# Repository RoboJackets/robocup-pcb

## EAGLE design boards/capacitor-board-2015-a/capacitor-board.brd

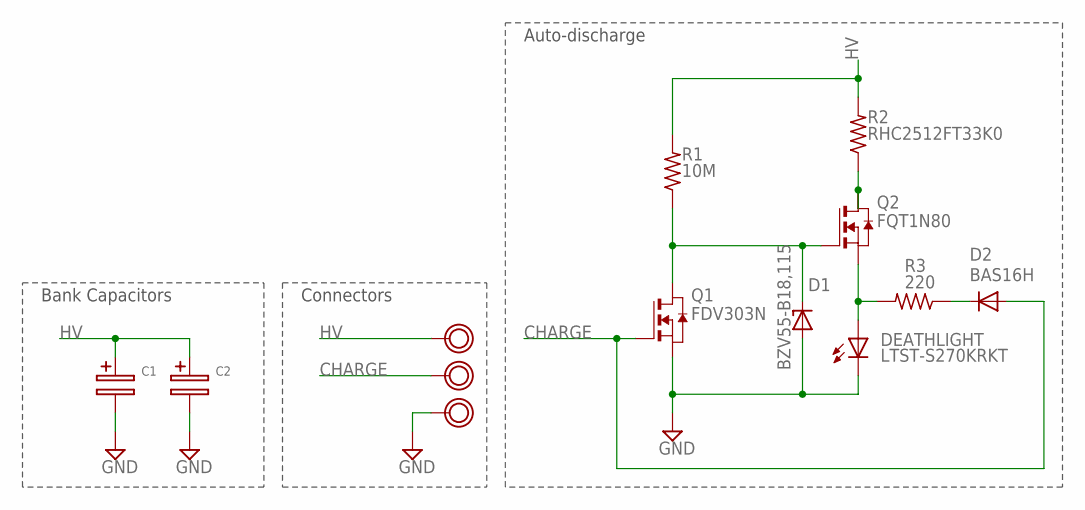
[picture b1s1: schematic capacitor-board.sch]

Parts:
C1, C2: RC_CAPHORIZ; 25MM-DIA_HORIZ
D1: BZV55-B18,115; SOD80C
D2: BAS16H; SOD323-W
DEATHLIGHT: LTST-S270KRKT; CHIPLED_0603
Q1: FDV303N; SOT-23
Q2: FQT1N80; SOT223
R1: 10M; R0603
R2: RHC2512FT33K0; R2512
R3: 220; R0603
U$1, U$2, U$3: VIA_TP; VIA_2MM

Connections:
CHARGE: D2.A, Q1.3 (G), U$2.P$1
GND: C1.-, C2.-, D1.A, DEATHLIGHT.C, Q1.2 (S), U$3.P$1
HV: C1.+, C2.+, R1.2, R2.2, U$1.P$1
unnamed: D1.C, Q1.1 (D), Q2.1 (G), R1.1
unnamed: Q2.2 (D), Q2.4 (D2), R2.1
unnamed: DEATHLIGHT.A, Q2.3 (S), R3.2
unnamed: D2.C, R3.1

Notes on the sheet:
Bank Capacitors
Connectors
Auto-discharge

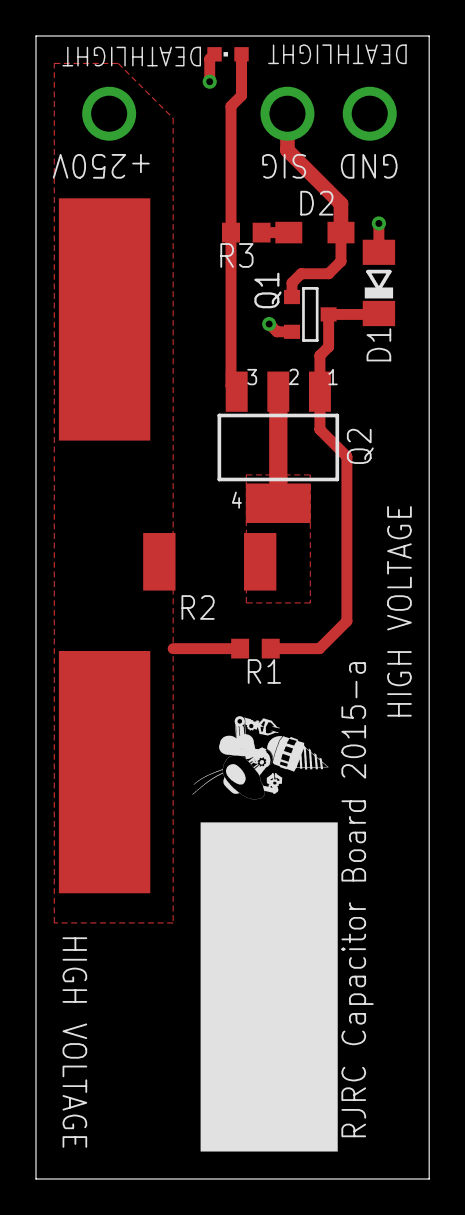
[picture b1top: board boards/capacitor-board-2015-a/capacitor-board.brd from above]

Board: 2 copper layers, 21.8 x 63.5 mm, 14 parts (0 on the bottom side), 7 nets.

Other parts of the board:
U$4: ROBOBUZZ_0.4X

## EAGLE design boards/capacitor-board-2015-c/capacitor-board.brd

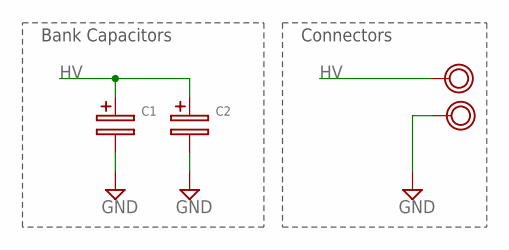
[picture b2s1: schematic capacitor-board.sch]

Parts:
C1, C2: RC_CAPHORIZ; 25MM-DIA_HORIZ
U$1, U$3: VIA_TP; VIA_2MM

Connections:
GND: C1.-, C2.-, U$3.P$1
HV: C1.+, C2.+, U$1.P$1

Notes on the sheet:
Bank Capacitors
Connectors

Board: 2 copper layers, 6 parts (1 on the bottom side), 2 nets, no tracks yet.

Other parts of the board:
U$2, U$4: ROBOBUZZ_0.4X

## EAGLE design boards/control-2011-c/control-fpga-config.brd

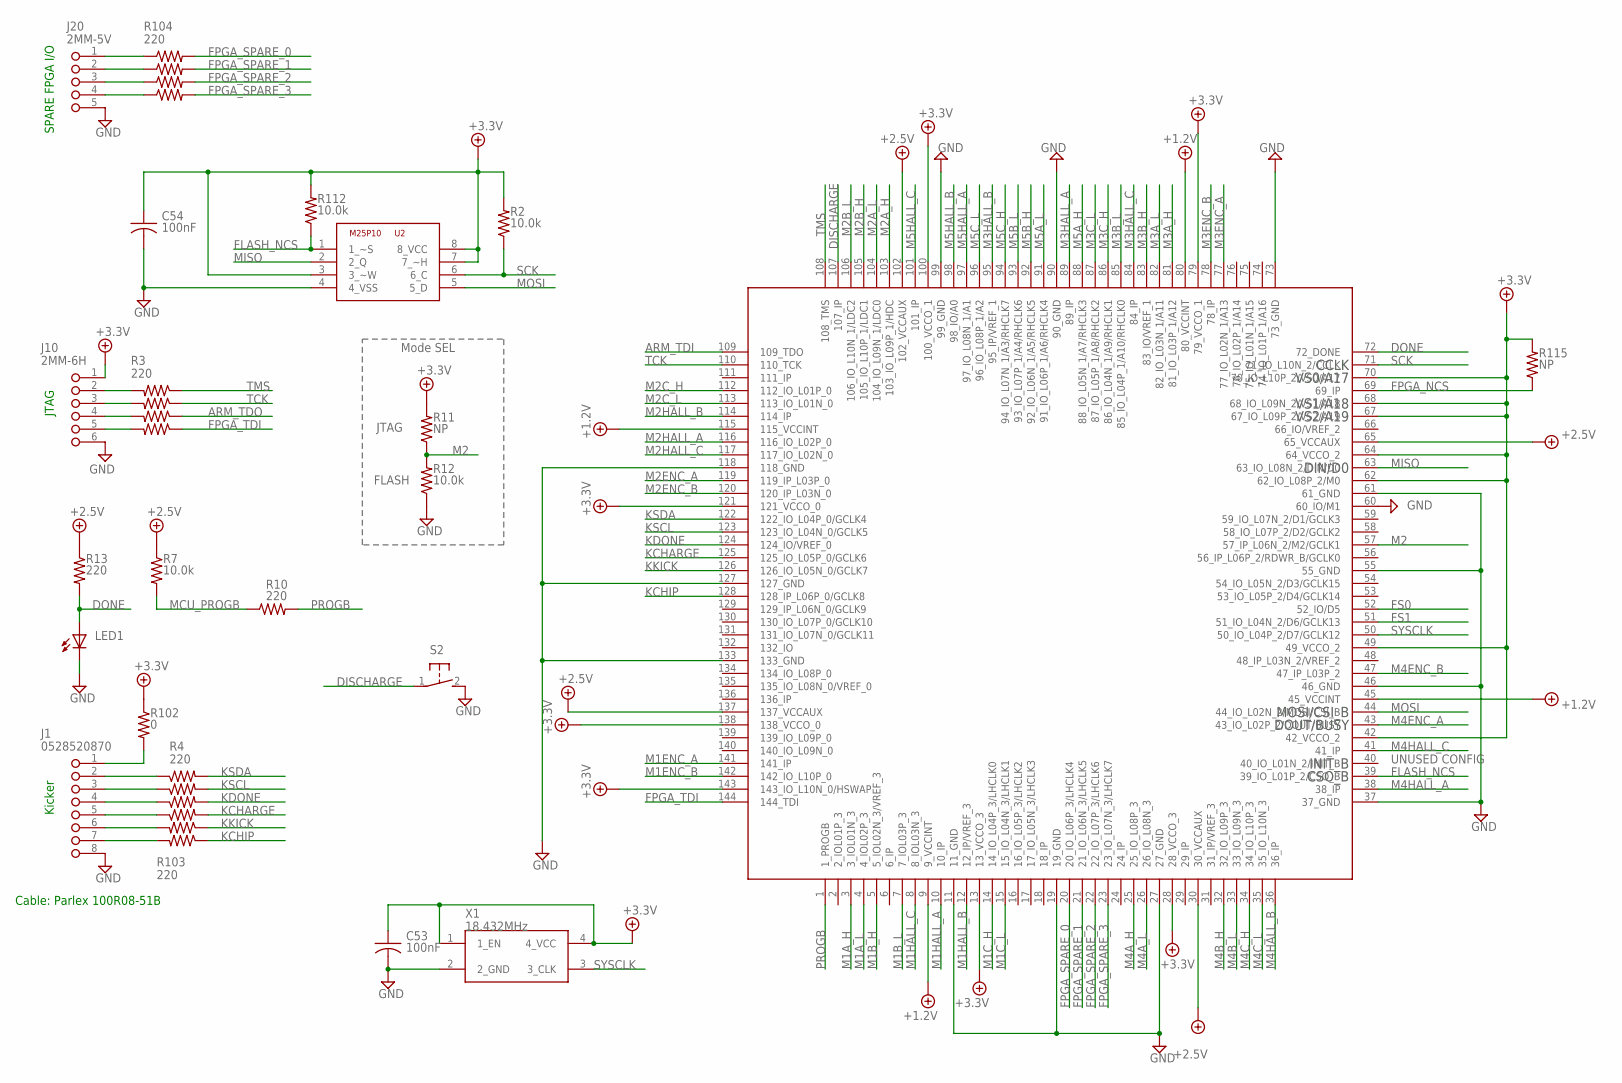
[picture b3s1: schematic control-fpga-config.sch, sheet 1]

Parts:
C53, C54: 100nF; C0603
J1: 0528520870
J10: 2MM-6H; 2MM-6-H
J20: 2MM-5V; 2MM-5-V
LED1: LEDCHIP-LED0603; CHIP-LED0603
R2, R7, R12, R112: 10.0k; R0603
R3, R4, R104: 220; RA_4_1206
R10, R13: 220; R0603
R11, R115: NP; R0603
R102: 0; R0603
R103: 220; RA_2_0606
S2: 31-XX; B3F-31XX
U1: XC3S100E; TQFP144
U2: M25P10; SO08
X1: 18.432MHz; XTAL_LCC

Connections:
+1.2V: U1.9 (9_VCCINT), U1.45 (45_VCCINT), U1.80 (80_VCCINT), U1.115 (115_VCCINT); also elsewhere on the board
+2.5V: R7.1, R13.1, U1.30 (30_VCCAUX), U1.65 (65_VCCAUX), U1.102 (102_VCCAUX), U1.137 (137_VCCAUX); also elsewhere on the board
+3.3V: C53.1, C54.1, J10.1, R2.2, R11.2, R102.1, R112.2, R115.2, U1.13 (13_VCCO_3), U1.28 (28_VCCO_3), U1.42 (42_VCCO_2), U1.49 (49_VCCO_2), U1.62 (62_IO_L08P_2/M0), U1.64 (64_VCCO_2), U1.67 (67_IO_L09P_2/VS2/A19), U1.68 (68_IO_L09N_2/VS1/A18), U1.70 (70_IO_L10P_2/VS0/A17), U1.79 (79_VCCO_1), U1.100 (100_VCCO_1), U1.121 (121_VCCO_0), U1.138 (138_VCCO_0), U1.143 (143_IO_L10N_0/HSWAP), U2.3 (3_~W), U2.7 (7_~H), U2.8 (8_VCC), X1.1 (1_EN), X1.4 (4_VCC); also elsewhere on the board
ARM_TDI: U1.109 (109_TDO); also elsewhere on the board
ARM_TDO: R3.5; also elsewhere on the board
DISCHARGE: S2.1, U1.107 (107_IP)
DONE: LED1.A, R13.2, U1.72 (72_DONE)
FLASH_NCS: R112.1, U1.39 (39_IO_L01P_2/CSO_B), U2.1 (1_~S); also elsewhere on the board
FPGA_NCS: R115.1, U1.69 (69_IP); also elsewhere on the board
FPGA_SPARE_0: R104.2, U1.20 (20_IO_L06P_3/LHCLK4)
FPGA_SPARE_1: R104.4, U1.21 (21_IO_L06N_3/LHCLK5)
FPGA_SPARE_2: R104.6, U1.22 (22_IO_L07P_3/LHCLK6)
FPGA_SPARE_3: R104.8, U1.23 (23_IO_L07N_3/LHCLK7)
FPGA_TDI: R3.7, U1.144 (144_TDI)
FS0: U1.52 (52_IO/D5); also elsewhere on the board
FS1: U1.51 (51_IO_L04N_2/D6/GCLK13); also elsewhere on the board
GND: C53.2, C54.2, J1.8, J10.6, J20.5, LED1.C, R12.1, S2.2 (S), U1.11 (11_GND), U1.19 (19_GND), U1.27 (27_GND), U1.37 (37_GND), U1.46 (46_GND), U1.55 (55_GND), U1.60 (60_IO/M1), U1.61 (61_GND), U1.73 (73_GND), U1.90 (90_GND), U1.99 (99_GND), U1.118 (118_GND), U1.127 (127_GND), U1.133 (133_GND), U2.4 (4_VSS), X1.2 (2_GND); also elsewhere on the board
KCHARGE: R4.2, U1.125 (125_IO_L05P_0/GCLK6)
KCHIP: R103.3, U1.128 (128_IP_L06P_0/GCLK8)
KDONE: R4.4, U1.124 (124_IO/VREF_0)
KKICK: R103.1, U1.126 (126_IO_L05N_0/GCLK7)
KSCL: R4.6, U1.123 (123_IO_L04N_0/GCLK5)
KSDA: R4.8, U1.122 (122_IO_L04P_0/GCLK4)
M1A_H: U1.3 (3_IOL01N_3); also elsewhere on the board
M1A_L: U1.4 (4_IOL02P_3); also elsewhere on the board
M1B_H: U1.5 (5_IOL02N_3/VREF_3); also elsewhere on the board
M1B_L: U1.7 (7_IOL03P_3); also elsewhere on the board
M1C_H: U1.14 (14_IO_L04P_3/LHCLK0); also elsewhere on the board
M1C_L: U1.15 (15_IO_L04N_3/LHCLK1); also elsewhere on the board
M1ENC_A: U1.141 (141_IP); also elsewhere on the board
M1ENC_B: U1.142 (142_IO_L10P_0); also elsewhere on the board
M1HALL_A: U1.10 (10_IP); also elsewhere on the board
M1HALL_B: U1.12 (12_IP/VREF_3); also elsewhere on the board
M1HALL_C: U1.8 (8_IOL03N_3); also elsewhere on the board
M2: R11.1, R12.2, U1.57 (57_IP_L06N_2/M2/GCLK1)
M2A_H: U1.103 (103_IO_L09P_1/HDC); also elsewhere on the board
M2A_L: U1.104 (104_IO_L09N_1/LDC0); also elsewhere on the board
M2B_H: U1.105 (105_IO_L10P_1/LDC1); also elsewhere on the board
M2B_L: U1.106 (106_IO_L10N_1/LDC2); also elsewhere on the board
M2C_H: U1.112 (112_IO_L01P_0); also elsewhere on the board
M2C_L: U1.113 (113_IO_L01N_0); also elsewhere on the board
M2ENC_A: U1.119 (119_IP_L03P_0); also elsewhere on the board
M2ENC_B: U1.120 (120_IP_L03N_0); also elsewhere on the board
M2HALL_A: U1.116 (116_IO_L02P_0); also elsewhere on the board
M2HALL_B: U1.114 (114_IP); also elsewhere on the board
M2HALL_C: U1.117 (117_IO_L02N_0); also elsewhere on the board
M3A_H: U1.81 (81_IO_L03P_1/A12); also elsewhere on the board
M3A_L: U1.82 (82_IO_L03N_1/A11); also elsewhere on the board
M3B_H: U1.83 (83_IO/VREF_1); also elsewhere on the board
M3B_L: U1.85 (85_IO_L04P_1/A10/RHCLK0); also elsewhere on the board
M3C_H: U1.86 (86_IO_L04N_1/A9/RHCLK1); also elsewhere on the board
M3C_L: U1.87 (87_IO_L05P_1/A8/RHCLK2); also elsewhere on the board
M3ENC_A: U1.77 (77_IO_L02N_1/A13); also elsewhere on the board
M3ENC_B: U1.78 (78_IP); also elsewhere on the board
M3HALL_A: U1.89 (89_IP); also elsewhere on the board
M3HALL_B: U1.95 (95_IP/VREF_1); also elsewhere on the board
M3HALL_C: U1.84 (84_IP); also elsewhere on the board
M4A_H: U1.25 (25_IO_L08P_3); also elsewhere on the board
M4A_L: U1.26 (26_IO_L08N_3); also elsewhere on the board
M4B_H: U1.32 (32_IO_L09P_3); also elsewhere on the board
M4B_L: U1.33 (33_IO_L09N_3); also elsewhere on the board
M4C_H: U1.34 (34_IO_L10P_3); also elsewhere on the board
M4C_L: U1.35 (35_IO_L10N_3); also elsewhere on the board
M4ENC_A: U1.43 (43_IO_L02P_2/DOUT/BUSY); also elsewhere on the board
M4ENC_B: U1.47 (47_IP_L03P_2); also elsewhere on the board
M4HALL_A: U1.38 (38_IP); also elsewhere on the board
M4HALL_B: U1.36 (36_IP); also elsewhere on the board
M4HALL_C: U1.41 (41_IP); also elsewhere on the board
M5A_H: U1.88 (88_IO_L05N_1/A7/RHCLK3); also elsewhere on the board
M5A_L: U1.91 (91_IO_L06P_1/A6/RHCLK4); also elsewhere on the board
M5B_H: U1.92 (92_IO_L06N_1/A5/RHCLK5); also elsewhere on the board
M5B_L: U1.93 (93_IO_L07P_1/A4/RHCLK6); also elsewhere on the board
M5C_H: U1.94 (94_IO_L07N_1/A3/RHCLK7); also elsewhere on the board
M5C_L: U1.96 (96_IO_L08P_1/A2); also elsewhere on the board
M5HALL_A: U1.97 (97_IO_L08N_1/A1); also elsewhere on the board
M5HALL_B: U1.98 (98_IO/A0); also elsewhere on the board
M5HALL_C: U1.101 (101_IP); also elsewhere on the board
MCU_PROGB: R7.2, R10.1; also elsewhere on the board
MISO: U1.63 (63_IO_L08N_2/DIN/D0), U2.2 (2_Q); also elsewhere on the board
MOSI: U1.44 (44_IO_L02N_2/MOSI/CSI_B), U2.5 (5_D); also elsewhere on the board
unnamed: J10.3, R3.4
unnamed: J10.5, R3.8
unnamed: J1.2, R4.7
unnamed: J1.3, R4.5
unnamed: J1.4, R4.3
unnamed: J1.5, R4.1
unnamed: J10.4, R3.6
unnamed: J10.2, R3.2
unnamed: J1.6, R103.2
unnamed: J1.7, R103.4
unnamed: J1.1, R102.2
unnamed: J20.3, R104.5
unnamed: J20.2, R104.3
unnamed: J20.1, R104.1
unnamed: J20.4, R104.7
PROGB: R10.2, U1.1 (1_PROGB)
SCK: R2.1, U1.71 (71_IO_L10N_2/CCLK), U2.6 (6_C); also elsewhere on the board
SYSCLK: U1.50 (50_IO_L04P_2/D7/GCLK12), X1.3 (3_CLK); also elsewhere on the board
TCK: R3.3, U1.110 (110_TCK); also elsewhere on the board
TMS: R3.1, U1.108 (108_TMS); also elsewhere on the board

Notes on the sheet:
JTAG
FLASH
Mode SEL
Kicker
UNUSED CONFIG
SPARE FPGA I/O
Cable: Parlex 100R08-51B
INIT_B
CCLK
CSO_B
MOSI/CSI_B
DOUT/BUSY
DIN/D0
VS1/A18
VS2/A19
VS0/A17

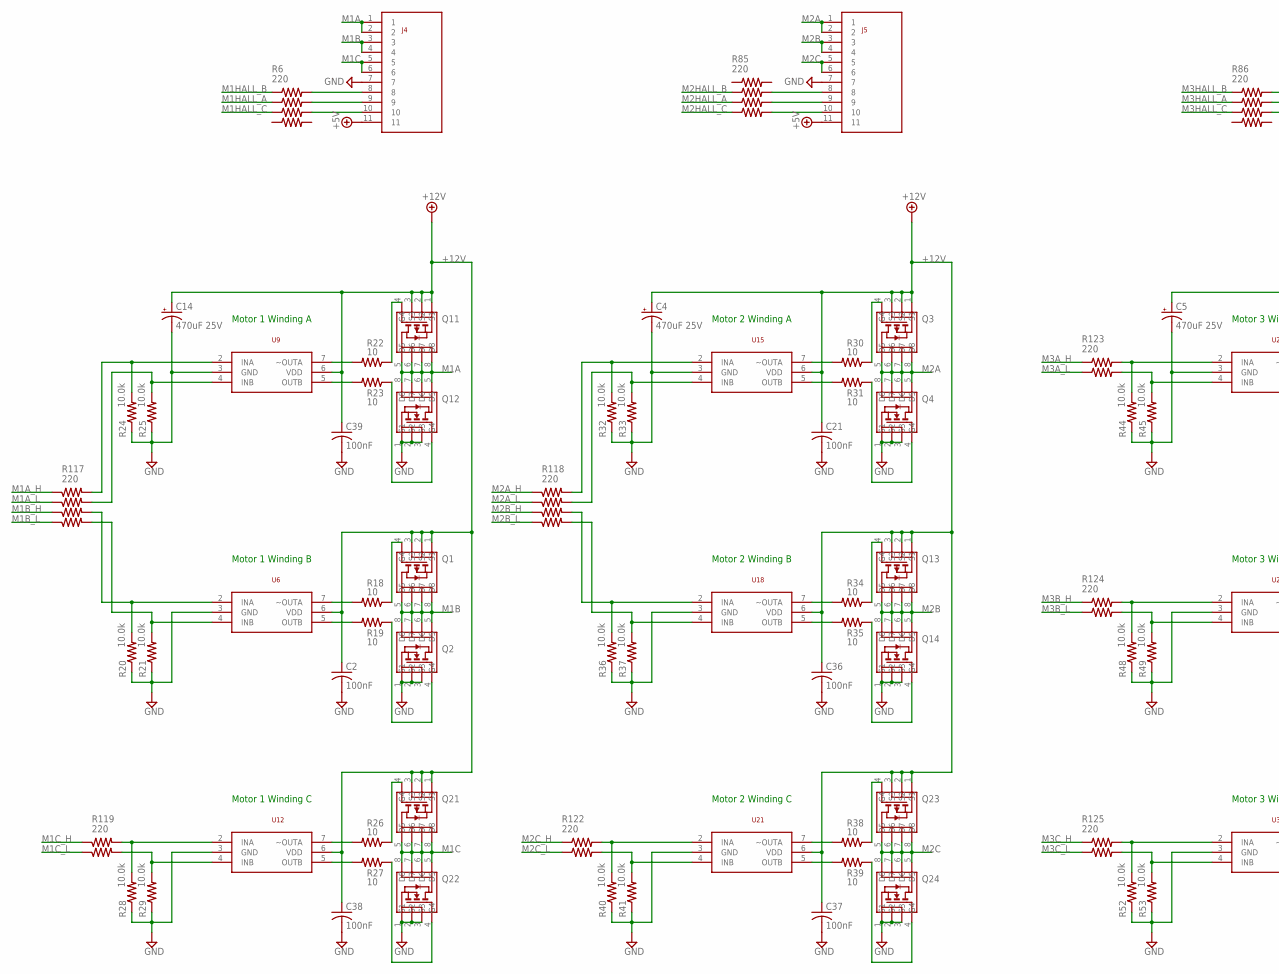
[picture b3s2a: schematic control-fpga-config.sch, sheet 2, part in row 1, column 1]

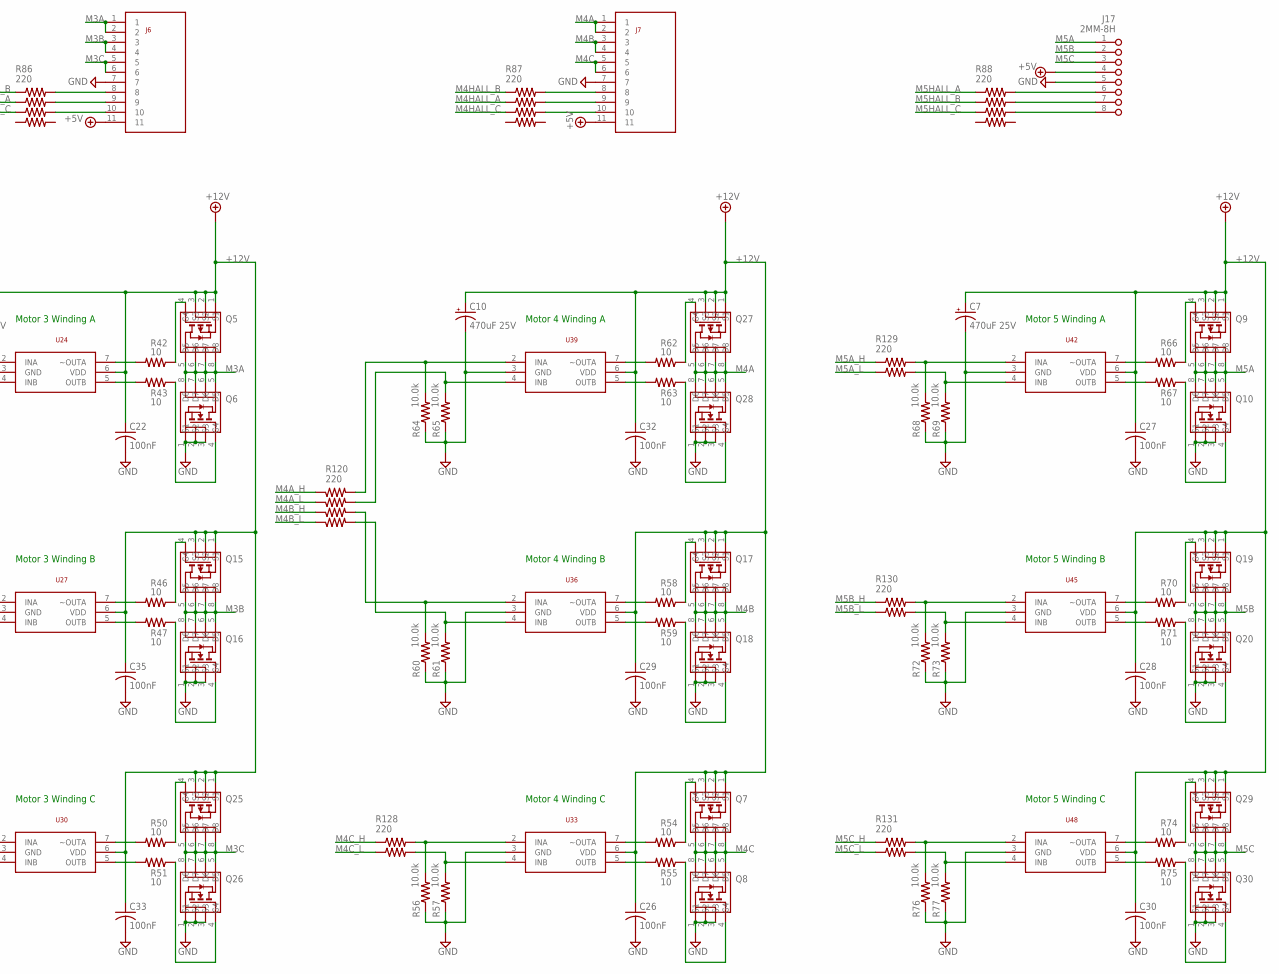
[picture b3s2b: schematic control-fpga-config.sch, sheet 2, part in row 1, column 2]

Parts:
C2, C21, C22, C26, C27, C28, C29, C30, C32, C33, C35, C36, C37, C38, C39: 100nF; C0603
C4, C5, C7, C10, C14: 470uF 25V; PANASONIC_G
J4, J5, J6, J7: Molex 0522711179; FH_11_HOR
J17: 2MM-8H; 2MM-8-H
Q1, Q3, Q5, Q7, Q9, Q11, Q13, Q15, Q17, Q19, Q21, Q23, Q25, Q27, Q29: IRF9310TRPBF; SO8
Q2, Q4, Q6, Q8, Q10, Q12, Q14, Q16, Q18, Q20, Q22, Q24, Q26, Q28, Q30: IRF8734TRPBF; SO8
R6, R85, R86, R87, R88, R117, R118, R120: 220; RA_4_1206
R18, R19, R22, R23, R26, R27, R30, R31, R34, R35, R38, R39, R42, R43, R46, R47, R50, R51, R54, R55, R58, R59, R62, R63, R66, R67, R70, R71, R74, R75: 10; R0603
R20, R21, R24, R25, R28, R29, R32, R33, R36, R37, R40, R41, R44, R45, R48, R49, R52, R53, R56, R57, R60, R61, R64, R65, R68, R69, R72, R73, R76, R77: 10.0k; R0603
R119, R122, R123, R124, R125, R128, R129, R130, R131: 220; RA_2_0606
U6, U9, U12, U15, U18, U21, U24, U27, U30, U33, U36, U39, U42, U45, U48: TC4428; SO08

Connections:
+5V: J4.11, J5.11, J6.11, J7.11, J17.4; also elsewhere on the board
+12V: C2.1, C4.+, C5.+, C7.+, C10.+, C14.+, C21.1, C22.1, C26.1, C27.1, C28.1, C29.1, C30.1, C32.1, C33.1, C35.1, C36.1, C37.1, C38.1, C39.1, Q1.1 (S1), Q1.2 (S2), Q1.3 (S3), Q3.1 (S1), Q3.2 (S2), Q3.3 (S3), Q5.1 (S1), Q5.2 (S2), Q5.3 (S3), Q7.1 (S1), Q7.2 (S2), Q7.3 (S3), Q9.1 (S1), Q9.2 (S2), Q9.3 (S3), Q11.1 (S1), Q11.2 (S2), Q11.3 (S3), Q13.1 (S1), Q13.2 (S2), Q13.3 (S3), Q15.1 (S1), Q15.2 (S2), Q15.3 (S3), Q17.1 (S1), Q17.2 (S2), Q17.3 (S3), Q19.1 (S1), Q19.2 (S2), Q19.3 (S3), Q21.1 (S1), Q21.2 (S2), Q21.3 (S3), Q23.1 (S1), Q23.2 (S2), Q23.3 (S3), Q25.1 (S1), Q25.2 (S2), Q25.3 (S3), Q27.1 (S1), Q27.2 (S2), Q27.3 (S3), Q29.1 (S1), Q29.2 (S2), Q29.3 (S3), U6.6 (VDD), U9.6 (VDD), U12.6 (VDD), U15.6 (VDD), U18.6 (VDD), U21.6 (VDD), U24.6 (VDD), U27.6 (VDD), U30.6 (VDD), U33.6 (VDD), U36.6 (VDD), U39.6 (VDD), U42.6 (VDD), U45.6 (VDD), U48.6 (VDD); also elsewhere on the board
GND: C2.2, C4.-, C5.-, C7.-, C10.-, C14.-, C21.2, C22.2, C26.2, C27.2, C28.2, C29.2, C30.2, C32.2, C33.2, C35.2, C36.2, C37.2, C38.2, C39.2, J4.7, J5.7, J6.7, J7.7, J17.5, Q2.1 (S1), Q2.2 (S2), Q2.3 (S3), Q4.1 (S1), Q4.2 (S2), Q4.3 (S3), Q6.1 (S1), Q6.2 (S2), Q6.3 (S3), Q8.1 (S1), Q8.2 (S2), Q8.3 (S3), Q10.1 (S1), Q10.2 (S2), Q10.3 (S3), Q12.1 (S1), Q12.2 (S2), Q12.3 (S3), Q14.1 (S1), Q14.2 (S2), Q14.3 (S3), Q16.1 (S1), Q16.2 (S2), Q16.3 (S3), Q18.1 (S1), Q18.2 (S2), Q18.3 (S3), Q20.1 (S1), Q20.2 (S2), Q20.3 (S3), Q22.1 (S1), Q22.2 (S2), Q22.3 (S3), Q24.1 (S1), Q24.2 (S2), Q24.3 (S3), Q26.1 (S1), Q26.2 (S2), Q26.3 (S3), Q28.1 (S1), Q28.2 (S2), Q28.3 (S3), Q30.1 (S1), Q30.2 (S2), Q30.3 (S3), R20.1, R21.1, R24.1, R25.1, R28.1, R29.1, R32.1, R33.1, R36.1, R37.1, R40.1, R41.1, R44.1, R45.1, R48.1, R49.1, R52.1, R53.1, R56.1, R57.1, R60.1, R61.1, R64.1, R65.1, R68.1, R69.1, R72.1, R73.1, R76.1, R77.1, U6.3 (GND), U9.3 (GND), U12.3 (GND), U15.3 (GND), U18.3 (GND), U21.3 (GND), U24.3 (GND), U27.3 (GND), U30.3 (GND), U33.3 (GND), U36.3 (GND), U39.3 (GND), U42.3 (GND), U45.3 (GND), U48.3 (GND); also elsewhere on the board
M1A: J4.1, J4.2, Q11.5 (D5), Q11.6 (D6), Q11.7 (D7), Q11.8 (D8), Q12.5 (D5), Q12.6 (D6), Q12.7 (D7), Q12.8 (D8)
M1A_H: R117.7; also elsewhere on the board
M1A_L: R117.5; also elsewhere on the board
M1B: J4.3, J4.4, Q1.5 (D5), Q1.6 (D6), Q1.7 (D7), Q1.8 (D8), Q2.5 (D5), Q2.6 (D6), Q2.7 (D7), Q2.8 (D8)
M1B_H: R117.3; also elsewhere on the board
M1B_L: R117.1; also elsewhere on the board
M1C: J4.5, J4.6, Q21.5 (D5), Q21.6 (D6), Q21.7 (D7), Q21.8 (D8), Q22.5 (D5), Q22.6 (D6), Q22.7 (D7), Q22.8 (D8)
M1C_H: R119.3; also elsewhere on the board
M1C_L: R119.1; also elsewhere on the board
M1HALL_A: R6.3; also elsewhere on the board
M1HALL_B: R6.1; also elsewhere on the board
M1HALL_C: R6.5; also elsewhere on the board
M2A: J5.1, J5.2, Q3.5 (D5), Q3.6 (D6), Q3.7 (D7), Q3.8 (D8), Q4.5 (D5), Q4.6 (D6), Q4.7 (D7), Q4.8 (D8)
M2A_H: R118.7; also elsewhere on the board
M2A_L: R118.5; also elsewhere on the board
M2B: J5.3, J5.4, Q13.5 (D5), Q13.6 (D6), Q13.7 (D7), Q13.8 (D8), Q14.5 (D5), Q14.6 (D6), Q14.7 (D7), Q14.8 (D8)
M2B_H: R118.3; also elsewhere on the board
M2B_L: R118.1; also elsewhere on the board
M2C: J5.5, J5.6, Q23.5 (D5), Q23.6 (D6), Q23.7 (D7), Q23.8 (D8), Q24.5 (D5), Q24.6 (D6), Q24.7 (D7), Q24.8 (D8)
M2C_H: R122.1; also elsewhere on the board
M2C_L: R122.3; also elsewhere on the board
M2HALL_A: R85.5; also elsewhere on the board
M2HALL_B: R85.3; also elsewhere on the board
M2HALL_C: R85.7; also elsewhere on the board
M3A: J6.1, J6.2, Q5.5 (D5), Q5.6 (D6), Q5.7 (D7), Q5.8 (D8), Q6.5 (D5), Q6.6 (D6), Q6.7 (D7), Q6.8 (D8)
M3A_H: R123.1; also elsewhere on the board
M3A_L: R123.3; also elsewhere on the board
M3B: J6.3, J6.4, Q15.5 (D5), Q15.6 (D6), Q15.7 (D7), Q15.8 (D8), Q16.5 (D5), Q16.6 (D6), Q16.7 (D7), Q16.8 (D8)
M3B_H: R124.1; also elsewhere on the board
M3B_L: R124.3; also elsewhere on the board
M3C: J6.5, J6.6, Q25.5 (D5), Q25.6 (D6), Q25.7 (D7), Q25.8 (D8), Q26.5 (D5), Q26.6 (D6), Q26.7 (D7), Q26.8 (D8)
M3C_H: R125.1; also elsewhere on the board
M3C_L: R125.3; also elsewhere on the board
M3HALL_A: R86.3; also elsewhere on the board
M3HALL_B: R86.1; also elsewhere on the board
M3HALL_C: R86.5; also elsewhere on the board
M4A: J7.1, J7.2, Q27.5 (D5), Q27.6 (D6), Q27.7 (D7), Q27.8 (D8), Q28.5 (D5), Q28.6 (D6), Q28.7 (D7), Q28.8 (D8)
M4A_H: R120.7; also elsewhere on the board
M4A_L: R120.5; also elsewhere on the board
M4B: J7.3, J7.4, Q17.5 (D5), Q17.6 (D6), Q17.7 (D7), Q17.8 (D8), Q18.5 (D5), Q18.6 (D6), Q18.7 (D7), Q18.8 (D8)
M4B_H: R120.3; also elsewhere on the board
M4B_L: R120.1; also elsewhere on the board
M4C: J7.5, J7.6, Q7.5 (D5), Q7.6 (D6), Q7.7 (D7), Q7.8 (D8), Q8.5 (D5), Q8.6 (D6), Q8.7 (D7), Q8.8 (D8)
M4C_H: R128.1; also elsewhere on the board
M4C_L: R128.3; also elsewhere on the board
M4HALL_A: R87.3; also elsewhere on the board
M4HALL_B: R87.1; also elsewhere on the board
M4HALL_C: R87.5; also elsewhere on the board
M5A: J17.1, Q9.5 (D5), Q9.6 (D6), Q9.7 (D7), Q9.8 (D8), Q10.5 (D5), Q10.6 (D6), Q10.7 (D7), Q10.8 (D8)
M5A_H: R129.1; also elsewhere on the board
M5A_L: R129.3; also elsewhere on the board
M5B: J17.2, Q19.5 (D5), Q19.6 (D6), Q19.7 (D7), Q19.8 (D8), Q20.5 (D5), Q20.6 (D6), Q20.7 (D7), Q20.8 (D8)
M5B_H: R130.1; also elsewhere on the board
M5B_L: R130.3; also elsewhere on the board
M5C: J17.3, Q29.5 (D5), Q29.6 (D6), Q29.7 (D7), Q29.8 (D8), Q30.5 (D5), Q30.6 (D6), Q30.7 (D7), Q30.8 (D8)
M5C_H: R131.1; also elsewhere on the board
M5C_L: R131.3; also elsewhere on the board
M5HALL_A: R88.1; also elsewhere on the board
M5HALL_B: R88.3; also elsewhere on the board
M5HALL_C: R88.5; also elsewhere on the board
unnamed: Q2.4 (G4), R19.1
unnamed: R22.2, U9.7 (~OUTA)
unnamed: R18.2, U6.7 (~OUTA)
unnamed: R23.2, U9.5 (OUTB)
unnamed: Q4.4 (G4), R31.1
unnamed: Q6.4 (G4), R43.1
unnamed: Q8.4 (G4), R55.1
unnamed: Q11.4 (G4), R22.1
unnamed: R19.2, U6.5 (OUTB)
unnamed: Q12.4 (G4), R23.1
unnamed: R26.2, U12.7 (~OUTA)
unnamed: R27.2, U12.5 (OUTB)
unnamed: Q1.4 (G4), R18.1
unnamed: Q10.4 (G4), R67.1
unnamed: Q21.4 (G4), R26.1
unnamed: Q22.4 (G4), R27.1
unnamed: R30.2, U15.7 (~OUTA)
unnamed: R31.2, U15.5 (OUTB)
unnamed: Q3.4 (G4), R30.1
unnamed: Q14.4 (G4), R35.1
unnamed: R34.2, U18.7 (~OUTA)
unnamed: R35.2, U18.5 (OUTB)
unnamed: Q13.4 (G4), R34.1
unnamed: Q16.4 (G4), R47.1
unnamed: R38.2, U21.7 (~OUTA)
unnamed: R39.2, U21.5 (OUTB)
unnamed: Q23.4 (G4), R38.1
unnamed: Q24.4 (G4), R39.1
unnamed: R42.2, U24.7 (~OUTA)
unnamed: R43.2, U24.5 (OUTB)
unnamed: Q5.4 (G4), R42.1
unnamed: Q18.4 (G4), R59.1
unnamed: R46.2, U27.7 (~OUTA)
unnamed: R47.2, U27.5 (OUTB)
unnamed: Q15.4 (G4), R46.1
unnamed: Q20.4 (G4), R71.1
unnamed: R50.2, U30.7 (~OUTA)
unnamed: R51.2, U30.5 (OUTB)
unnamed: Q25.4 (G4), R50.1
unnamed: J17.6, R88.2
unnamed: R54.2, U33.7 (~OUTA)
unnamed: R55.2, U33.5 (OUTB)
unnamed: Q7.4 (G4), R54.1
unnamed: Q26.4 (G4), R51.1
unnamed: R58.2, U36.7 (~OUTA)
unnamed: R59.2, U36.5 (OUTB)
unnamed: Q17.4 (G4), R58.1
unnamed: Q28.4 (G4), R63.1
unnamed: R62.2, U39.7 (~OUTA)
unnamed: R63.2, U39.5 (OUTB)
unnamed: Q27.4 (G4), R62.1
unnamed: Q30.4 (G4), R75.1
unnamed: R66.2, U42.7 (~OUTA)
unnamed: R67.2, U42.5 (OUTB)
unnamed: Q9.4 (G4), R66.1
unnamed: R70.2, U45.7 (~OUTA)
unnamed: R71.2, U45.5 (OUTB)
unnamed: Q19.4 (G4), R70.1
unnamed: R74.2, U48.7 (~OUTA)
unnamed: R75.2, U48.5 (OUTB)
unnamed: Q29.4 (G4), R74.1
unnamed: J4.8, R6.2
unnamed: J4.9, R6.4
unnamed: J4.10, R6.6
unnamed: J5.8, R85.4
unnamed: J5.10, R85.8
unnamed: J5.9, R85.6
unnamed: J6.8, R86.2
unnamed: J6.10, R86.6
unnamed: J6.9, R86.4
unnamed: J7.8, R87.2
unnamed: J7.10, R87.6
unnamed: J7.9, R87.4
unnamed: J17.7, R88.4
unnamed: J17.8, R88.6
unnamed: R25.2, R117.6, U9.4 (INB)
unnamed: R24.2, R117.8, U9.2 (INA)
unnamed: R21.2, R117.2, U6.4 (INB)
unnamed: R20.2, R117.4, U6.2 (INA)
unnamed: R29.2, R119.2, U12.4 (INB)
unnamed: R28.2, R119.4, U12.2 (INA)
unnamed: R40.2, R122.2, U21.2 (INA)
unnamed: R41.2, R122.4, U21.4 (INB)
unnamed: R36.2, R118.4, U18.2 (INA)
unnamed: R37.2, R118.2, U18.4 (INB)
unnamed: R32.2, R118.8, U15.2 (INA)
unnamed: R33.2, R118.6, U15.4 (INB)
unnamed: R44.2, R123.2, U24.2 (INA)
unnamed: R45.2, R123.4, U24.4 (INB)
unnamed: R48.2, R124.2, U27.2 (INA)
unnamed: R49.2, R124.4, U27.4 (INB)
unnamed: R52.2, R125.2, U30.2 (INA)
unnamed: R53.2, R125.4, U30.4 (INB)
unnamed: R56.2, R128.2, U33.2 (INA)
unnamed: R57.2, R128.4, U33.4 (INB)
unnamed: R60.2, R120.4, U36.2 (INA)
unnamed: R61.2, R120.2, U36.4 (INB)
unnamed: R64.2, R120.8, U39.2 (INA)
unnamed: R65.2, R120.6, U39.4 (INB)
unnamed: R76.2, R131.2, U48.2 (INA)
unnamed: R77.2, R131.4, U48.4 (INB)
unnamed: R72.2, R130.2, U45.2 (INA)
unnamed: R73.2, R130.4, U45.4 (INB)
unnamed: R68.2, R129.2, U42.2 (INA)
unnamed: R69.2, R129.4, U42.4 (INB)

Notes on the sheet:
Motor 1 Winding B
Motor 1 Winding A
Motor 1 Winding C
Motor 2 Winding A
Motor 2 Winding B
Motor 2 Winding C
Motor 3 Winding A
Motor 3 Winding B
Motor 3 Winding C
Motor 4 Winding C
Motor 4 Winding B
Motor 4 Winding A
Motor 5 Winding A
Motor 5 Winding B
Motor 5 Winding C

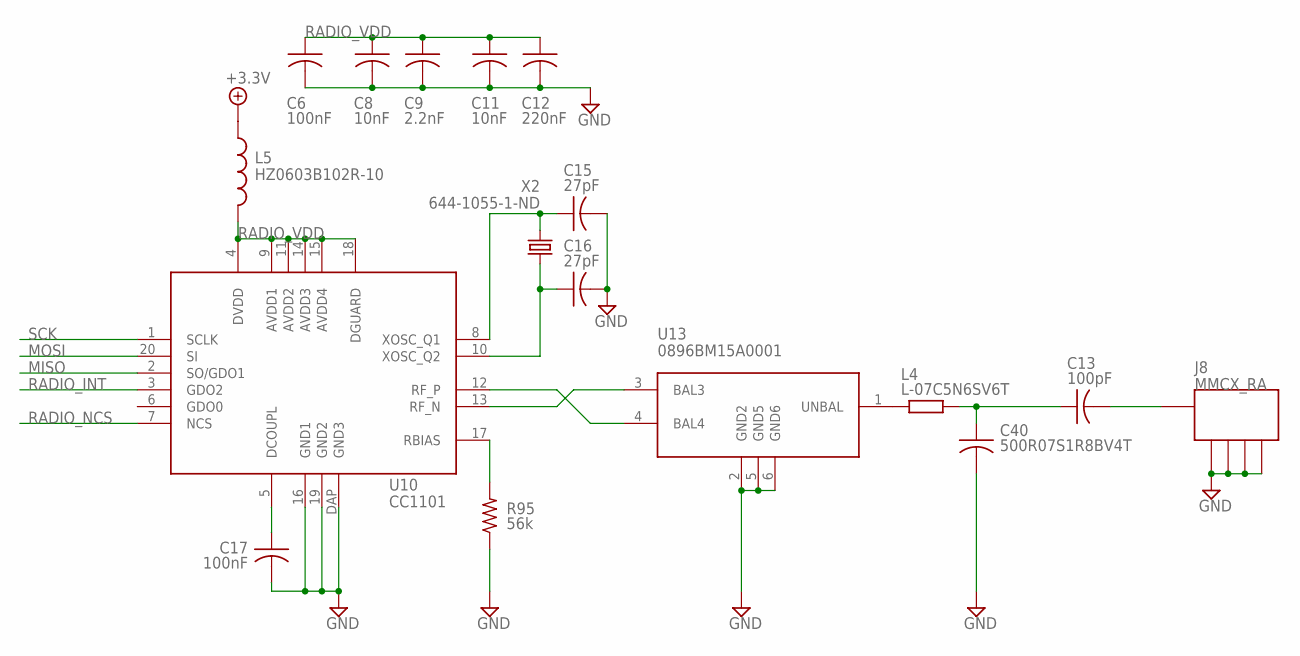
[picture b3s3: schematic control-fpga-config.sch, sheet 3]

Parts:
C6, C17: 100nF; C0603
C8, C11: 10nF; C0603
C9: 2.2nF; C0603
C12: 220nF; C0603
C13: 100pF; C0603
C15, C16: 27pF; C0603
C40: 500R07S1R8BV4T; C0402
J8: MMCX_RA
L4: L-07C5N6SV6T; R0402
L5: HZ0603B102R-10; C0603
R95: 56k; R0603
U10: CC1101; QLP20
U13: 0896BM15A0001
X2: 644-1055-1-ND; XTAL-3.2X2.5

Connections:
+3.3V: L5.1; also elsewhere on the board
GND: C6.2, C8.2, C9.2, C11.2, C12.2, C15.2, C16.2, C17.2, C40.2, J8.P$2, J8.P$3, J8.P$4, J8.P$5, R95.1, U10.16 (GND1), U10.19 (GND2), U10.DAP (GND3), U13.2 (GND2), U13.5 (GND5), U13.6 (GND6); also elsewhere on the board
MISO: U10.2 (SO/GDO1); also elsewhere on the board
MOSI: U10.20 (SI); also elsewhere on the board
unnamed: C17.1, U10.5 (DCOUPL)
unnamed: R95.2, U10.17 (RBIAS)
unnamed: C16.1, U10.10 (XOSC_Q2), X2.1
unnamed: C15.1, U10.8 (XOSC_Q1), X2.3 (2)
unnamed: L4.1, U13.1 (UNBAL)
unnamed: C13.1, C40.1, L4.2
unnamed: U10.12 (RF_P), U13.4 (BAL4)
unnamed: U10.13 (RF_N), U13.3 (BAL3)
unnamed: C13.2, J8.P$1
RADIO_INT: U10.3 (GDO2); also elsewhere on the board
RADIO_NCS: U10.7 (NCS); also elsewhere on the board
RADIO_VDD: C6.1, C8.1, C9.1, C11.1, C12.1, L5.2, U10.4 (DVDD), U10.9 (AVDD1), U10.11 (AVDD2), U10.14 (AVDD3), U10.15 (AVDD4), U10.18 (DGUARD)
SCK: U10.1 (SCLK); also elsewhere on the board

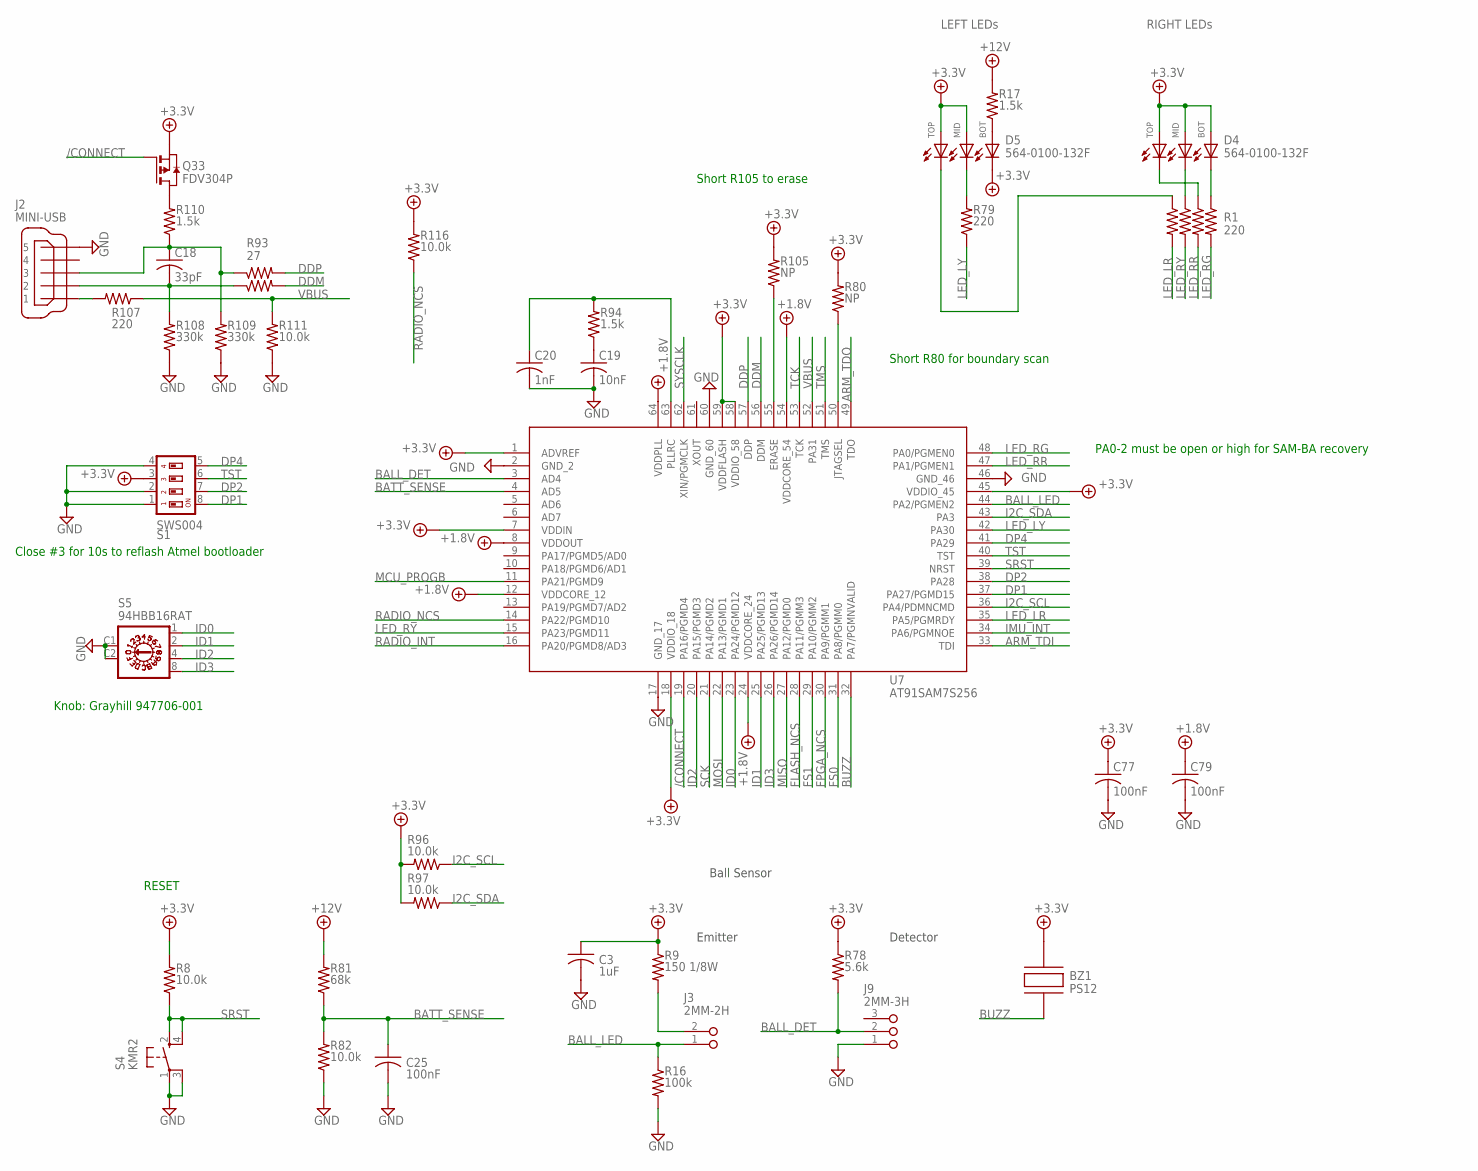
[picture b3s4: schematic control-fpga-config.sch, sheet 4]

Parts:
BZ1: PS12
C3: 1uF; C0603
C18: 33pF; C0603
C19: 10nF; C0603
C20: 1nF; C0603
C25, C77, C79: 100nF; C0603
D4, D5: 564-0100-132F; DIALIGHT-564
J2: MINI-USB; UX60A-MB-5ST
J3: 2MM-2H; 2MM-2-H
J9: 2MM-3H; 2MM-3-H
Q33: FDV304P; SOT-23
R1: 220; RA_4_1206
R8, R82, R96, R97, R111, R116: 10.0k; R0603
R9: 150 1/8W; R0805
R16: 100k; R0603
R17, R94, R110: 1.5k; R0603
R78: 5.6k; R0603
R79, R107: 220; R0603
R80, R105: NP; R0603
R81: 68k; R0603
R93: 27; RA_2_0606
R108, R109: 330k; R0603
S1: SWS004; SMS-004
S4: KMR2
S5: 94HBB16RAT; HEX-RA-2C
U7: AT91SAM7S256; SQFP-S-10X10-64

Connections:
+1.8V: C79.1, U7.8 (VDDOUT), U7.12 (VDDCORE_12), U7.24 (VDDCORE_24), U7.54 (VDDCORE_54), U7.64 (VDDPLL)
+3.3V: BZ1.2, C3.1, C77.1, D4.A1, D4.A2, D4.A3, D5.A1, D5.A2, D5.C3, Q33.2 (S), R8.2, R9.1, R78.1, R80.2, R96.2, R97.2, R105.2, R116.2, S1.3, U7.1 (ADVREF), U7.7 (VDDIN), U7.18 (VDDIO_18), U7.45 (VDDIO_45), U7.58 (VDDIO_58), U7.59 (VDDFLASH); also elsewhere on the board
+12V: R17.2, R81.2; also elsewhere on the board
/CONNECT: Q33.3 (G), U7.19 (PA16/PGMD4)
ARM_TDI: U7.33 (TDI); also elsewhere on the board
ARM_TDO: U7.49 (TDO); also elsewhere on the board
BALL_DET: J9.2, R78.2, U7.3 (AD4)
BALL_LED: J3.1, R16.1, U7.44 (PA2/PGMEN2)
BATT_SENSE: C25.1, R81.1, R82.2, U7.4 (AD5)
BUZZ: BZ1.1, U7.32 (PA7/PGMNVALID)
DDM: R93.2, U7.56 (DDM)
DDP: R93.4, U7.57 (DDP)
DP1: S1.8, U7.37 (PA27/PGMD15)
DP2: S1.7, U7.38 (PA28)
DP4: S1.5, U7.41 (PA29)
FLASH_NCS: U7.28 (PA11/PGMM3); also elsewhere on the board
FPGA_NCS: U7.30 (PA9/PGMM1); also elsewhere on the board
FS0: U7.31 (PA8/PGMM0); also elsewhere on the board
FS1: U7.29 (PA10/PGMM2); also elsewhere on the board
GND: C3.2, C19.2, C20.2, C25.2, C77.2, C79.2, J2.5, J9.1, R16.2, R82.1, R108.1, R109.1, R111.1, S1.1, S1.2, S1.4, S4.1, S4.3, S5.C1, S5.C2, U7.2 (GND_2), U7.17 (GND_17), U7.46 (GND_46), U7.60 (GND_60); also elsewhere on the board
I2C_SCL: R96.1, U7.36 (PA4/PDMNCMD); also elsewhere on the board
I2C_SDA: R97.1, U7.43 (PA3); also elsewhere on the board
ID0: S5.1, U7.23 (PA24/PGMD12)
ID1: S5.2, U7.25 (PA25/PGMD13)
ID2: S5.4, U7.20 (PA15/PGMD3)
ID3: S5.8, U7.26 (PA26/PGMD14)
IMU_INT: U7.34 (PA6/PGMNOE); also elsewhere on the board
LED_LR: R1.8, U7.35 (PA5/PGMRDY)
LED_LY: R79.1, U7.42 (PA30)
LED_RG: R1.2, U7.48 (PA0/PGMEN0)
LED_RR: R1.4, U7.47 (PA1/PGMEN1)
LED_RY: R1.6, U7.15 (PA23/PGMD11)
MCU_PROGB: U7.11 (PA21/PGMD9); also elsewhere on the board
MISO: U7.27 (PA12/PGMD0); also elsewhere on the board
MOSI: U7.22 (PA13/PGMD1); also elsewhere on the board
unnamed: J3.2, R9.2
unnamed: D4.C3, R1.1
unnamed: R80.1, U7.50 (JTAGSEL)
unnamed: C18.2, J2.2, R93.1, R108.2
unnamed: D4.C2, R1.5
unnamed: R105.1, U7.55 (ERASE)
unnamed: C18.1, J2.3, R93.3, R109.2, R110.1
unnamed: Q33.1 (D), R110.2
unnamed: C19.1, R94.1
unnamed: C20.1, R94.2, U7.63 (PLLRC)
unnamed: D4.C1, R1.3
unnamed: D5.C1, R1.7
unnamed: D5.C2, R79.2
unnamed: D5.A3, R17.1
unnamed: J2.1, R107.2
RADIO_INT: U7.16 (PA20/PGMD8/AD3); also elsewhere on the board
RADIO_NCS: R116.1, U7.14 (PA22/PGMD10); also elsewhere on the board
SCK: U7.21 (PA14/PGMD2); also elsewhere on the board
SRST: R8.1, S4.2, S4.4, U7.39 (NRST)
SYSCLK: U7.62 (XIN/PGMCLK); also elsewhere on the board
TCK: U7.53 (TCK); also elsewhere on the board
TMS: U7.51 (TMS); also elsewhere on the board
TST: S1.6, U7.40 (TST)
VBUS: R107.1, R111.2, U7.52 (PA31)

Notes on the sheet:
RESET
Ball Sensor
Emitter
Detector
PA0-2 must be open or high for SAM-BA recovery
Close #3 for 10s to reflash Atmel bootloader
RIGHT LEDs
LEFT LEDs
Short R105 to erase
Short R80 for boundary scan
Knob: Grayhill 947706-001

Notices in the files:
parts and their libraries:
SparkFun-IC-Logic: Licensing: Creative Commons ShareAlike 4.0 International - https://creativecommons.org/licenses/by-sa/4.0
